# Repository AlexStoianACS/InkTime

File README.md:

## InkTime

Smartwatch ieftin si open source.

### Power Management

Charger LiPo: BQ25180

Regulator 3.3V: RT6160

Fuel gauge: MAX17048

#### Interfata

I2C (SDA/SCL bus comun)

Pini INT pentru evenimente (PMIC_INT, ALERT)

### Display (e-paper)

Conector FPC pentru display e-paper

Circuit de drive + PFET pentru power gating (VEPD)

#### Interfata

SPI:

SCK -> P0.02

MOSI -> P0.03

CS -> P0.05

Control:

DC -> P0.15

RST -> P0.16

BUSY -> P0.17

### Senzori

IMU (accelerometru): BMA421

#### Interfata

I2C:

SDA -> P0.06

SCL -> P0.07

### Haptic Feedback

DRV2605L

#### Interfata

I2C (bus comun)

Enable:

HAPTIC_EN -> P0.12

### Butoane

Up -> P0.13

Down -> P0.14

Enter -> P1.00

### Interfata
D+ -> USB DP (nRF52840)

D- -> USB DM (nRF52840)

VBUS -> detect pin

### Schematic

Schematicul l-am realizat pe o singura pagina.

Toate rezistentele sunt SMD, in capsula 0201. Toate condensatoarele sunt SMD, cele cu valori mai mici sau egale cu 100nF sunt in capsula 0201, cele cu valori mai mari de 100nF sunt 0402.

Am ignorat erorile de ERC de genul "Power pin X connected to Y" sau "Only one pin on net X".

### PCB

PCB-ul este de tip 2-layer si am facut rutarea pe ambele parti, in timp ce componentele sunt doar pe top.

Am plasat butoanele, usb-c connector si e-paper display connector pentru a se alinia cu marginile corespunzator.

Condensatoarele de decuplare (100nF) au fost plasate cat mai aproape de pinii de alimentare. De asemenea, cristalele au fost plasate cat mai aproape de MCU.

Am izolat antena de restul circuitului, nu am trasat rute pe top / bottom unde se afla si nu am facut "polygon pour" in acea zona. Pad-ul "2" a fost plasat in exterior.

Rutele au grosimea 0.3mm pentru semnalele de tip "POWER" si 0.15mm in rest. In anumite cazuri am scazut grosimea pentru a le putea strecura prin anumite locuri.

M-am ajutat de "escape routing" prin plasarea unui via direct pe pin / pad si inceperea rutarii direct pe bottom.

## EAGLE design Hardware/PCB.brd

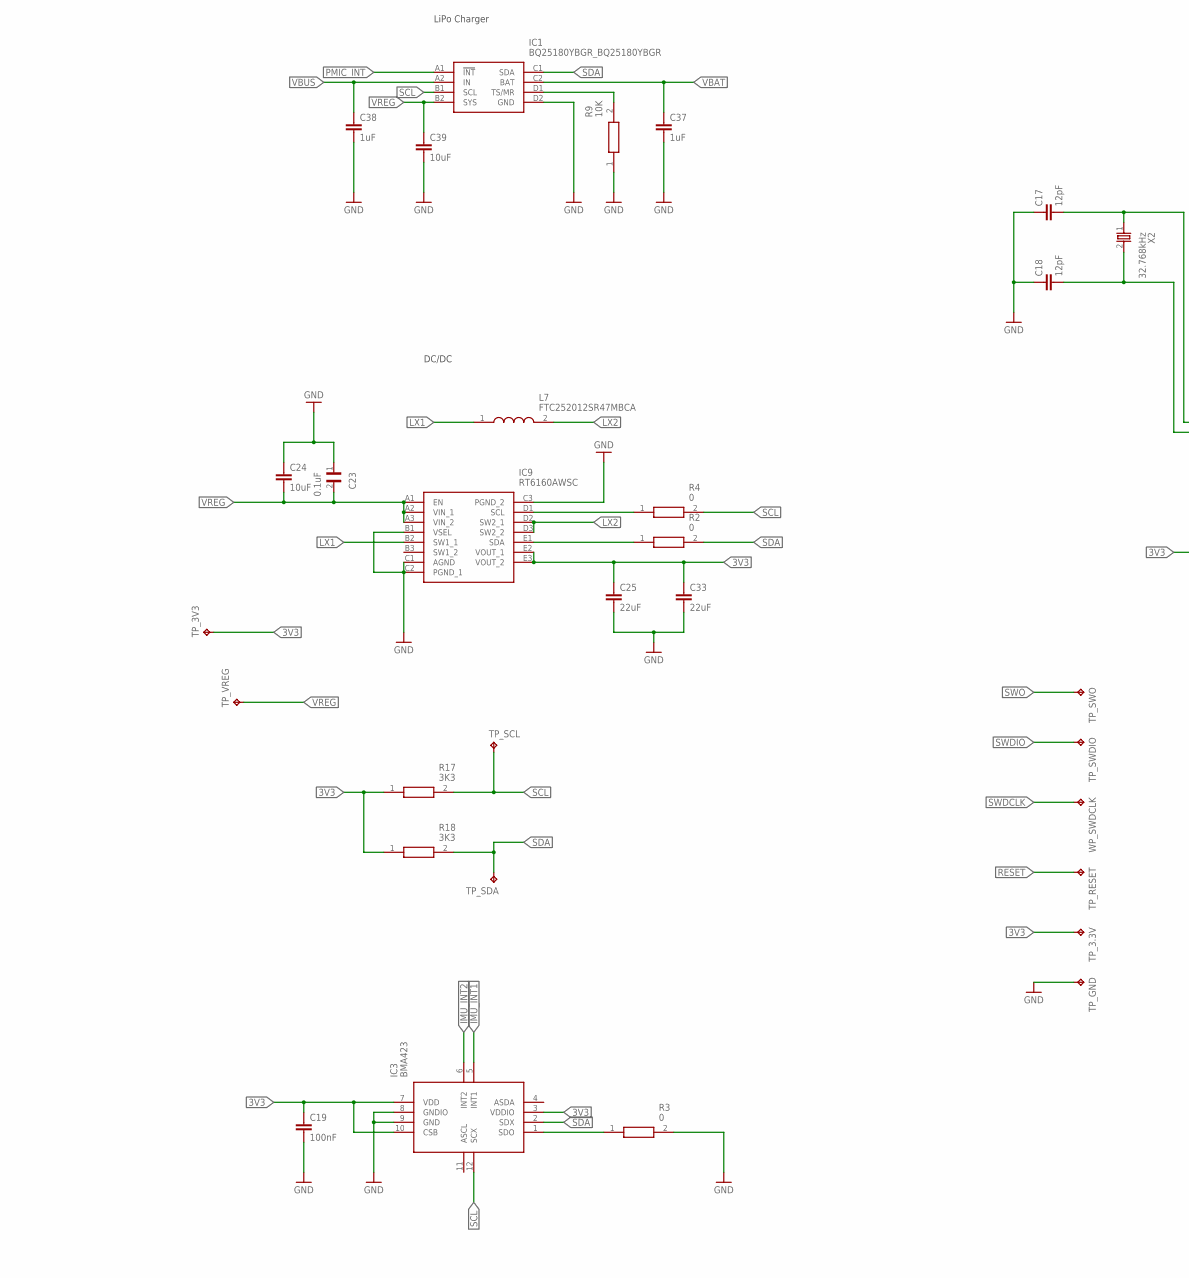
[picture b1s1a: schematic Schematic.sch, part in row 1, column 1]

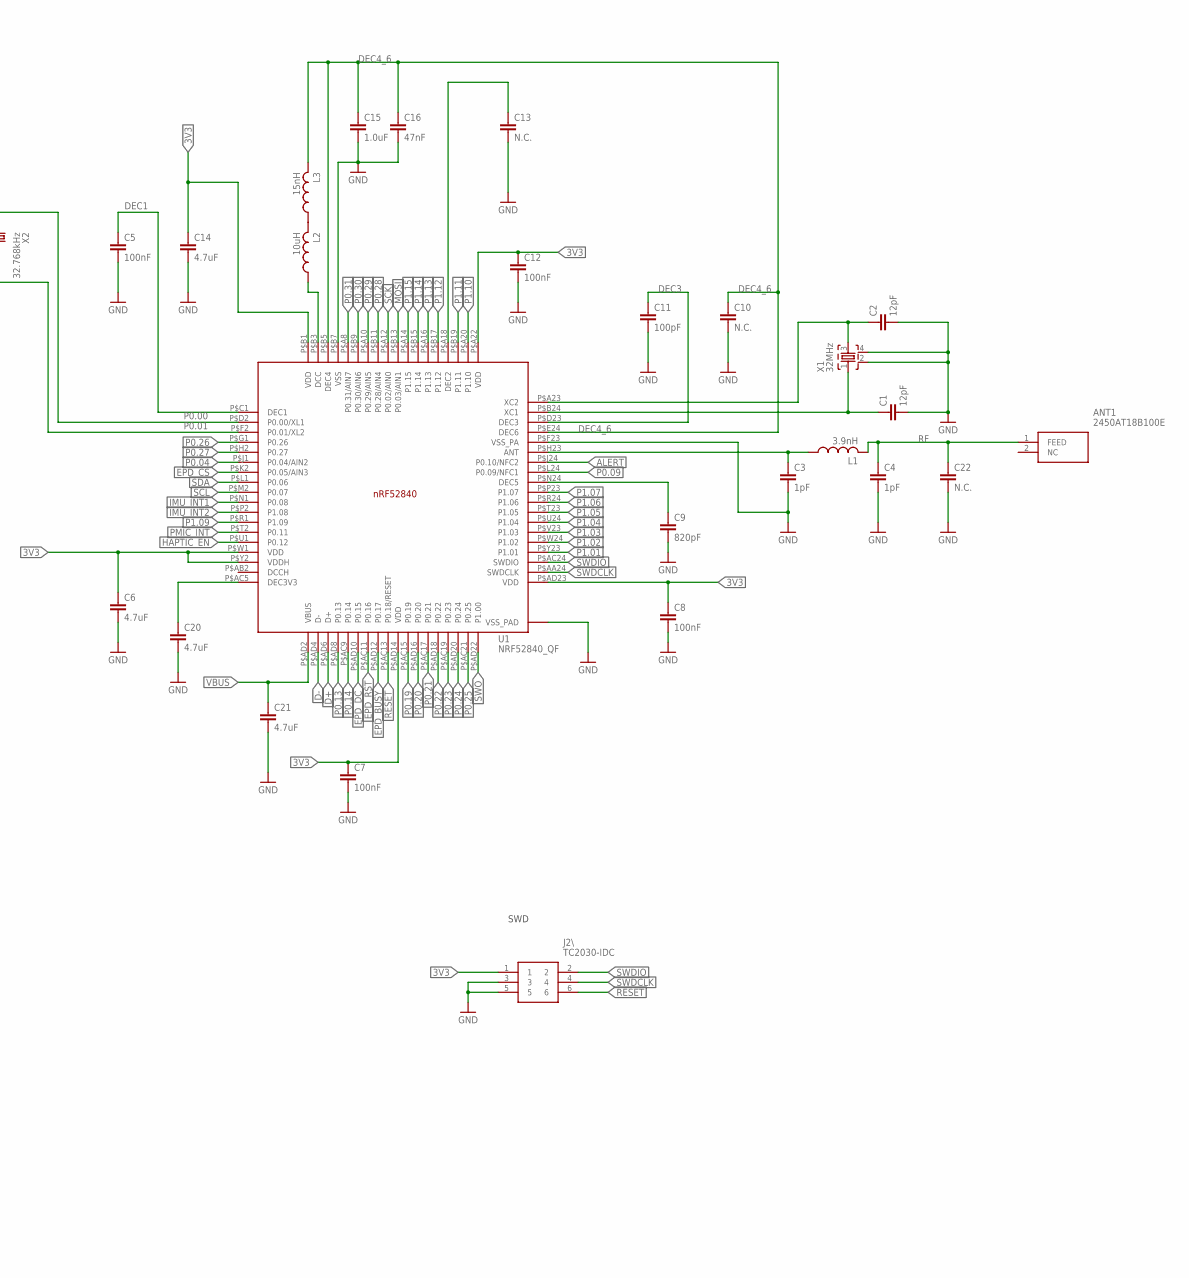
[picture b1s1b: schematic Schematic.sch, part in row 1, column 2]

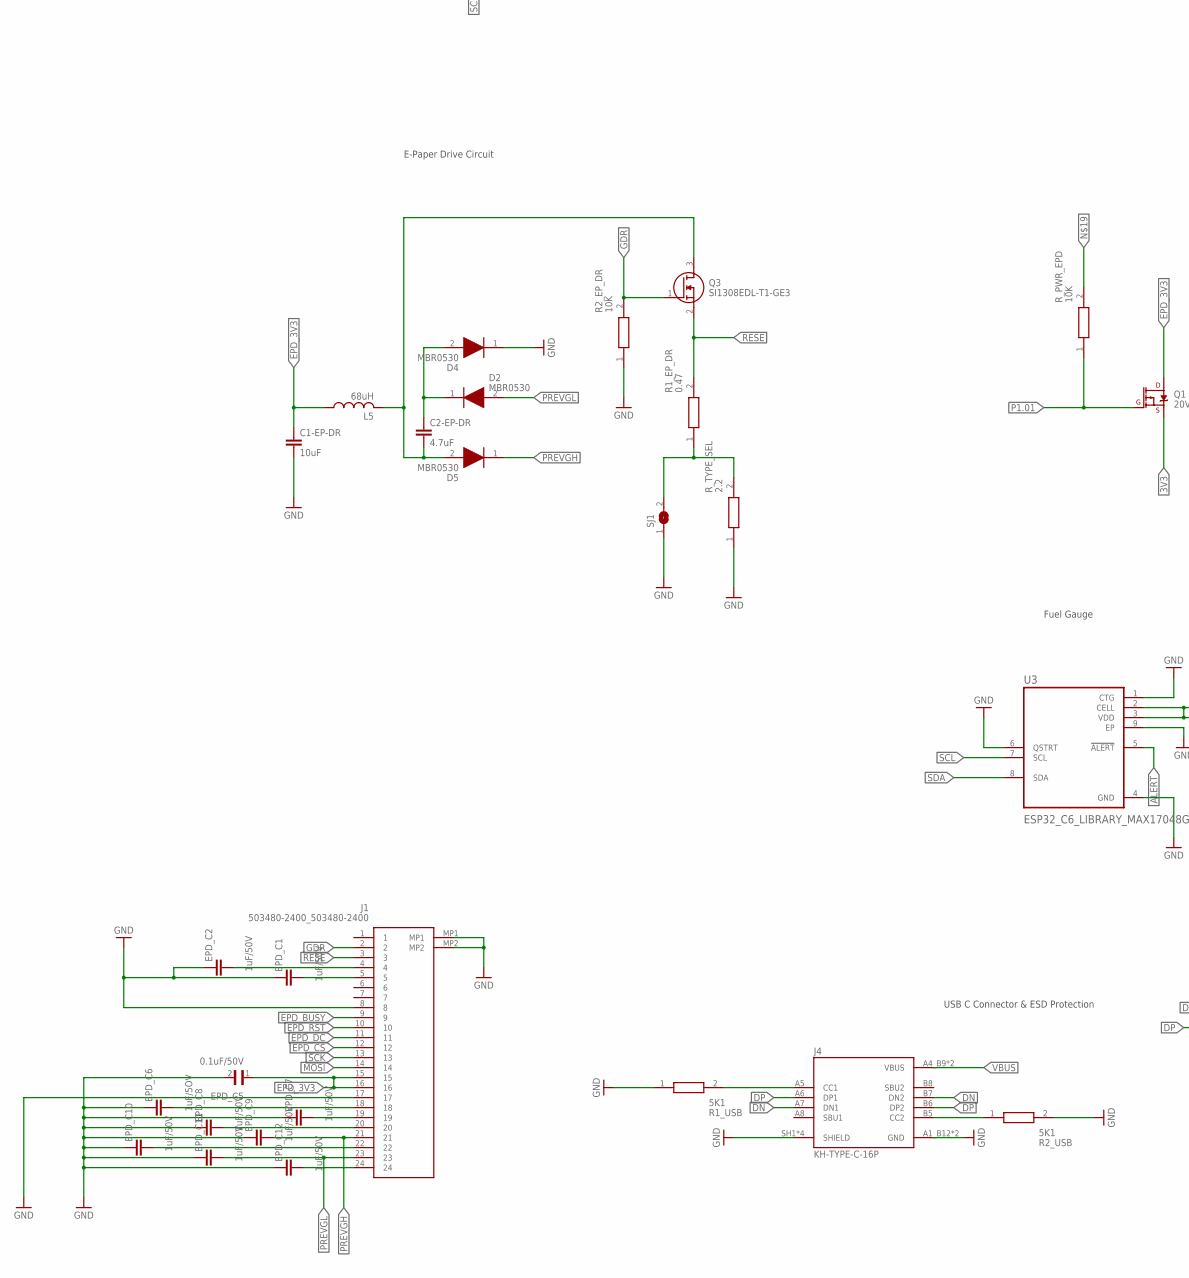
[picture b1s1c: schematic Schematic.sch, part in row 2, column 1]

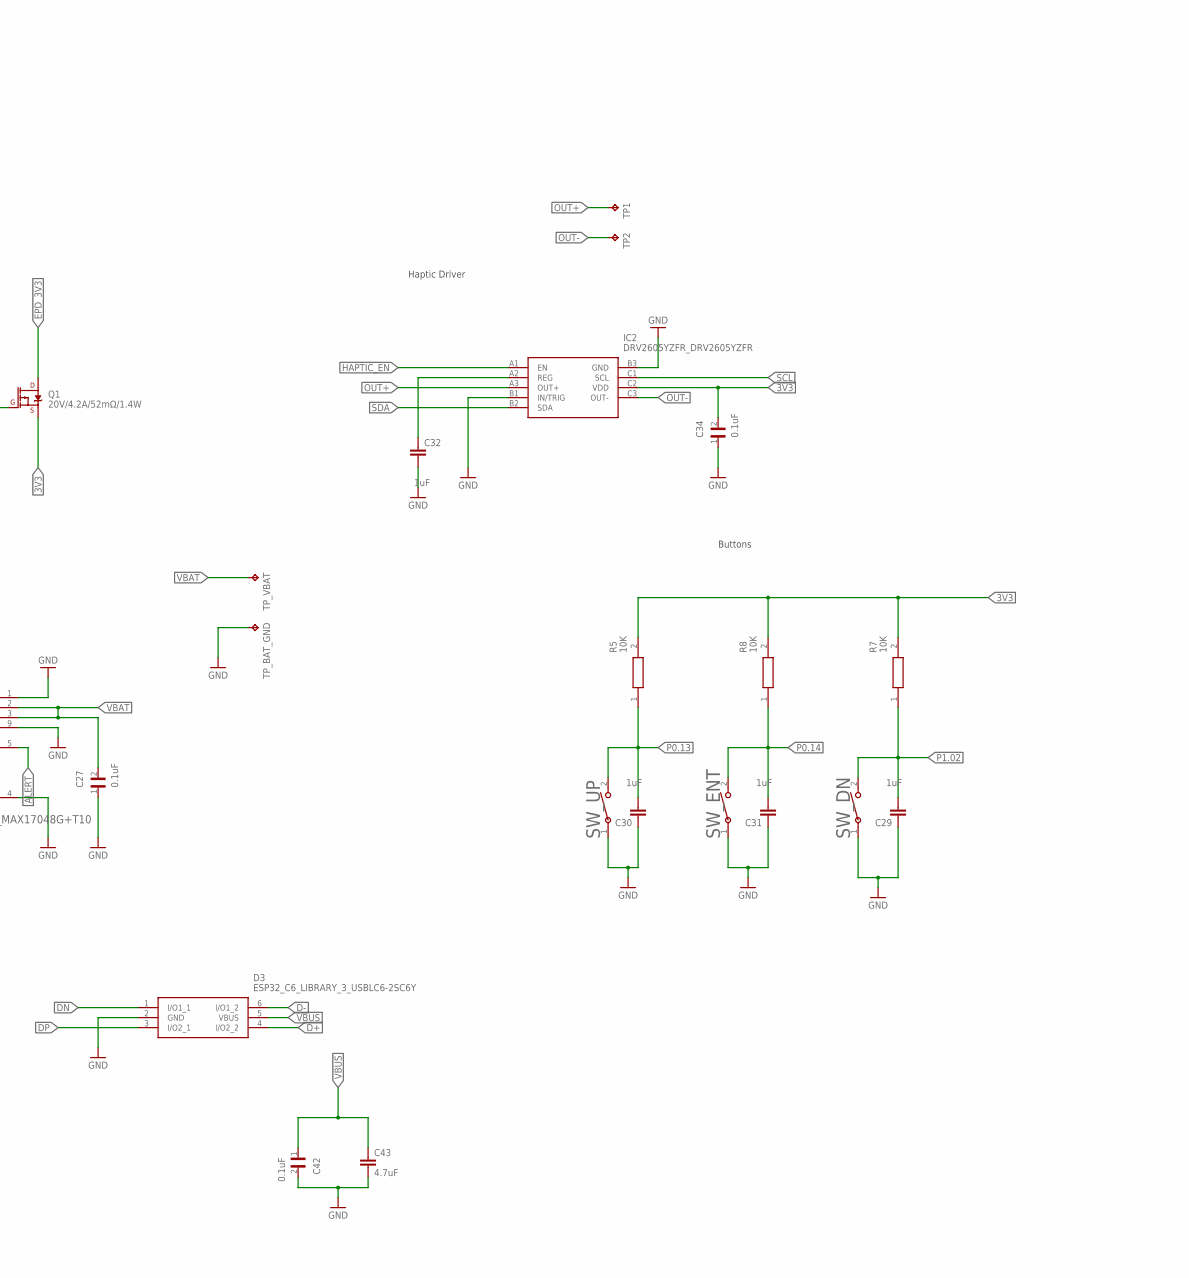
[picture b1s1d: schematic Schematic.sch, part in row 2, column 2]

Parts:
ANT1: 2450AT18B100E; 2450AT18B100E_ANTC3216X140N
C1, C2, C17, C18: 12pF; NORDIC_NRF_3_RESC0201_L
C1-EP-DR, C24, C39: 10uF; ESP32_C6_LIBRARY_1_ESP32_WROVER_EAGLE-LTSPICE_C0402
C2-EP-DR, C6, C14, C20, C21, C43: 4.7uF; ESP32_C6_LIBRARY_1_ESP32_WROVER_EAGLE-LTSPICE_C0402
C3, C4: 1pF; NORDIC_NRF_3_RESC0201_L
C5, C7, C8, C12, C19: 100nF; NORDIC_NRF_3_RESC0201_L
C9: 820pF; NORDIC_NRF_3_RESC0201_L
C10, C13, C22: N.C.; ESP32_C6_LIBRARY_1_ESP32_WROVER_EAGLE-LTSPICE_C0402
C11: 100pF; NORDIC_NRF_3_RESC0201_L
C15: 1.0uF; ESP32_C6_LIBRARY_1_ESP32_WROVER_EAGLE-LTSPICE_C0402
C16: 47nF; NORDIC_NRF_3_RESC0201_L
C23, C27, C34, C42: 0.1uF; GRM011R60J152KE01L_2_CAPC0201X13N
C25, C33: 22uF; ESP32_C6_LIBRARY_1_ESP32_WROVER_EAGLE-LTSPICE_C0402
C29, C30, C31, C32, C37, C38: 1uF; ESP32_C6_LIBRARY_1_ESP32_WROVER_EAGLE-LTSPICE_C0402
D2, D4, D5: MBR0530; ESP32_C6_LIBRARY_5_SOD3716X135N
D3: ESP32_C6_LIBRARY_3_USBLC6-2SC6Y; ESP32_C6_LIBRARY_3_SOT95P280X145-6N
EPD_C1, EPD_C2, EPD_C7, EPD_C8, EPD_C9, EPD_C10, EPD_C11, EPD_C12: 1uF/50V; ESP32_C6_LIBRARY_1_ESP32_WROVER_EAGLE-LTSPICE_C0402
EPD_C5: 0.1uF/50V; GRM011R60J152KE01L_2_CAPC0201X13N
EPD_C6: 1uF/5OV; ESP32_C6_LIBRARY_1_ESP32_WROVER_EAGLE-LTSPICE_C0402
IC1: BQ25180YBGR_BQ25180YBGR; BQ25180YBGR_BGA8C40P2X4_100X155X50
IC2: DRV2605YZFR_DRV2605YZFR; DRV2605YZFR_BGA9C50P3X3_144X144X62
IC3: BMA423; BMA423_BMA423
IC9: RT6160AWSC; RT6160AWSC_BGA15C40P3X5_140X230X60
J1: 503480-2400_503480-2400; 503480-2400_5034802400
J2\: TC2030-IDC; TC2030-IDC_TC2030IDC
J4: KH-TYPE-C-16P; KH-TYPE-C-16P_KINGHELM_KH-TYPE-C-16P
L1: 3.9nH; NORDIC_NRF_2_RESC0402_L
L2: 10uH; NORDIC_NRF_2_RESC0402_L
L3: 15nH; NORDIC_NRF_2_RESC0402_L
L5: 68uH; NORDIC_NRF_2_RESC0402_L
L7: FTC252012SR47MBCA; MLP2016SR47MT0S1_INDC2016X100N
Q1: 20V/4.2A/52mΩ/1.4W; ESP32_C6_LIBRARY_4_ESP32_C6_LIBRARY_4_ESP32_C6_LIBRARY_4_ES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
Q3: SI1308EDL-T1-GE3; ESP32_C6_LIBRARY_6_SOT65P210X110-3N
R1_EP_DR: 0.47; CPF0201D7K68C1_0201
R1_USB, R2_USB: 5K1; CPF0201D7K68C1_0201
R2, R3, R4: 0; CPF0201D7K68C1_0201
R2_EP_DR, R5, R7, R8, R9: 10K; CPF0201D7K68C1_0201
R17, R18: 3K3; CPF0201D7K68C1_0201
R_PWR_EPD: 10K; CPF0201D7K68C1_0201
R_TYPE_SEL: 2.2; CPF0201D7K68C1_0201
SJ1: SJ; ESP32_C6_LIBRARY_7_JUMPER_SJ
SW_DN: 2025-10-22_07-23-44_LIBRARY_EVP-AKE31ASW_EVP-AKE3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; 2025-10-22_07-23-44_LIBRARY_SW_EVP-AKE31A_PAN
SW_ENT: 2025-10-22_07-23-44_LIBRARY_EVP-AKE31ASW_EVP-AKE3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; 2025-10-22_07-23-44_LIBRARY_SW_EVP-AKE31A_PAN
SW_UP: 2025-10-22_07-23-44_LIBRARY_EVP-AKE31ASW_EVP-AKE3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; 2025-10-22_07-23-44_LIBRARY_SW_EVP-AKE31A_PAN
TP1, TP2: HECTOR_WATCH_1_TPTP20R; HECTOR_WATCH_1_TP20R
TP_3.3V, TP_3V3: HECTOR_WATCH_1_TPTP20R; HECTOR_WATCH_1_TP20R
TP_BAT_GND: HECTOR_WATCH_1_TPTP20R; HECTOR_WATCH_1_TP20R
TP_GND: HECTOR_WATCH_1_TPTP20R; HECTOR_WATCH_1_TP20R
TP_RESET: HECTOR_WATCH_1_TPTP20R; HECTOR_WATCH_1_TP20R
TP_SCL: HECTOR_WATCH_1_TPTP20R; HECTOR_WATCH_1_TP20R
TP_SDA: HECTOR_WATCH_1_TPTP20R; HECTOR_WATCH_1_TP20R
TP_SWDIO: HECTOR_WATCH_1_TPTP20R; HECTOR_WATCH_1_TP20R
TP_SWO: HECTOR_WATCH_1_TPTP20R; HECTOR_WATCH_1_TP20R
TP_VBAT: HECTOR_WATCH_1_TPTP20R; HECTOR_WATCH_1_TP20R
TP_VREG: HECTOR_WATCH_1_TPTP20R; HECTOR_WATCH_1_TP20R
U1: NRF52840_QF; NORDIC_NRF_4_AQFN50P700X700X85_HS-74N
U3: ESP32_C6_LIBRARY_MAX17048G+T10; ESP32_C6_LIBRARY_SON50P200X200X80-9N
WP_SWDCLK: HECTOR_WATCH_1_TPTP20R; HECTOR_WATCH_1_TP20R
X1: 32MHz; NORDIC_NRF_BT-XTAL_2016_N
X2: 32.768kHz; NORDIC_NRF_1_XTAL_3215_N

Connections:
3V3: C6.1, C7.1, C8.1, C12.1, C14.1, C19.1, C25.1, C33.1, C34.2, IC2.C2 (VDD), IC3.3 (VDDIO), IC3.7 (VDD), IC3.10 (CSB), IC9.E2 (VOUT_1), IC9.E3 (VOUT_2), J2\.1, Q1.2 (S), R5.2, R7.2, R8.2, R17.1, R18.1, TP_3.3V.TP, TP_3V3.TP, U1.P$A22 (VDD), U1.P$AD14 (VDD), U1.P$AD23 (VDD), U1.P$B1 (VDD), U1.P$W1 (VDD), U1.P$Y2 (VDDH)
ALERT: U1.P$J24 (P0.10/NFC2), U3.5 (!ALERT)
D+: D3.4 (I/O2_2), U1.P$AD6 (D+)
D-: D3.6 (I/O1_2), U1.P$AD4 (D-)
DEC1: C5.1, U1.P$C1 (DEC1)
DEC3: C11.1, U1.P$D23 (DEC3)
DEC4_6: C10.1, C15.1, C16.1, L3.2, U1.P$B5 (DEC4), U1.P$E24 (DEC6)
DN: D3.1 (I/O1_1), J4.A7 (DN1), J4.B7 (DN2)
DP: D3.3 (I/O2_1), J4.A6 (DP1), J4.B6 (DP2)
EPD_3V3: C1-EP-DR.1, EPD_C5.1, J1.15, J1.16, L5.1, Q1.3 (D)
EPD_BUSY: J1.9, U1.P$AD12 (P0.17)
EPD_CS: J1.12, U1.P$K2 (P0.05/AIN3)
EPD_DC: J1.11, U1.P$AD10 (P0.15)
EPD_RST: J1.10, U1.P$AC11 (P0.16)
GDR: J1.2, Q3.1 (G), R2_EP_DR.2
GND: C1.2, C1-EP-DR.2, C2.2, C3.2, C4.2, C5.2, C6.2, C7.2, C8.2, C9.2, C10.2, C11.2, C12.2, C13.2, C14.2, C15.2, C16.2, C17.1, C18.1, C19.2, C20.2, C21.2, C22.2, C23.1, C24.1, C25.2, C27.1, C29.1, C30.1, C31.1, C32.2, C33.2, C34.1, C37.2, C38.2, C39.2, C42.2, C43.2, D3.2 (GND), D4.1 (K), EPD_C1.1, EPD_C2.1, EPD_C5.2, EPD_C6.1, EPD_C7.1, EPD_C8.1, EPD_C9.1, EPD_C10.1, EPD_C11.1, EPD_C12.1, IC1.D2 (GND), IC2.B1 (IN/TRIG), IC2.B3 (GND), IC3.8 (GNDIO), IC3.9 (GND), IC9.B1 (VSEL), IC9.C1 (AGND), IC9.C2 (PGND_1), IC9.C3 (PGND_2), J1.8, J1.17, J1.MP1, J1.MP2, J2\.3, J2\.5, J4.A1_B12 (GND), J4.A12_B1 (GND), J4.SH1 (SHIELD), J4.SH2 (SHIELD), J4.SH3 (SHIELD), J4.SH4 (SHIELD), R1_USB.1, R2_EP_DR.1, R2_USB.2, R3.2, R9.1, R_TYPE_SEL.1, SJ1.1, SW_DN.1, SW_ENT.1, SW_UP.1, TP_BAT_GND.TP, TP_GND.TP, U1.P$74 (VSS_PAD), U1.P$75 (VSS_PAD), U1.P$76 (VSS_PAD), U1.P$77 (VSS_PAD), U1.P$78 (VSS_PAD), U1.P$79 (VSS_PAD), U1.P$80 (VSS_PAD), U1.P$81 (VSS_PAD), U1.P$82 (VSS_PAD), U1.P$83 (VSS_PAD), U1.P$84 (VSS_PAD), U1.P$85 (VSS_PAD), U1.P$86 (VSS_PAD), U1.P$87 (VSS_PAD), U1.P$88 (VSS_PAD), U1.P$89 (VSS_PAD), U1.P$90 (VSS_PAD), U1.P$B7 (VSS), U1.P$F23 (VSS_PA), U3.1 (CTG), U3.4 (GND), U3.6 (QSTRT), U3.9 (EP), X1.2, X1.4
HAPTIC_EN: IC2.A1 (EN), U1.P$U1 (P0.12)
IMU_INT1: IC3.5 (INT1), U1.P$N1 (P0.08)
IMU_INT2: IC3.6 (INT2), U1.P$P2 (P1.08)
LX1: IC9.B2 (SW1_1), L7.1
LX2: IC9.D2 (SW2_1), IC9.D3 (SW2_2), L7.2
MOSI: J1.14, U1.P$B13 (P0.03/AIN1)
unnamed: J4.A5 (CC1), R1_USB.2
unnamed: C2-EP-DR.2, D5.2 (A), L5.2, Q3.3 (D)
unnamed: L2.2, L3.1
unnamed: IC3.1 (SDO), R3.1
unnamed: C2.1, U1.P$A23 (XC2), X1.3
unnamed: IC1.D1 (TS/MR), R9.2
unnamed: L2.1, U1.P$B3 (DCC)
unnamed: IC9.E1 (SDA), R2.1
unnamed: C1.1, U1.P$B24 (XC1), X1.1
unnamed: IC9.D1 (SCL), R4.1
unnamed: C13.1, U1.P$A18 (DEC2)
unnamed: C3.1, L1.1, U1.P$H23 (ANT)
unnamed: C20.1, U1.P$AC5 (DEC3V3)
unnamed: C2-EP-DR.1, D2.1 (K), D4.2 (A)
unnamed: C32.1, IC2.A2 (REG)
unnamed: C9.1, U1.P$N24 (DEC5)
unnamed: R1_EP_DR.1, R_TYPE_SEL.2, SJ1.2
unnamed: EPD_C2.2, J1.4
unnamed: EPD_C1.2, J1.5
unnamed: J4.B5 (CC2), R2_USB.1
unnamed: EPD_C12.2, J1.24
unnamed: EPD_C10.2, J1.22
unnamed: EPD_C8.2, J1.20
unnamed: EPD_C7.2, J1.19
unnamed: EPD_C6.2, J1.18
OUT+: IC2.A3 (OUT+), TP1.TP
OUT-: IC2.C3 (OUT-), TP2.TP
P0.00: C17.2, U1.P$D2 (P0.00/XL1), X2.1
P0.01: C18.2, U1.P$F2 (P0.01/XL2), X2.2
P0.04: U1.P$J1 (P0.04/AIN2)
P0.09: U1.P$L24 (P0.09/NFC1)
P0.13: C30.2, R5.1, SW_UP.2, U1.P$AD8 (P0.13)
P0.14: C31.2, R8.1, SW_ENT.2, U1.P$AC9 (P0.14)
P0.19: U1.P$AC15 (P0.19)
P0.20: U1.P$AD16 (P0.20)
P0.21: U1.P$AC17 (P0.21)
P0.22: U1.P$AD18 (P0.22)
P0.23: U1.P$AC19 (P0.23)
P0.24: U1.P$AD20 (P0.24)
P0.25: U1.P$AC21 (P0.25)
P0.26: U1.P$G1 (P0.26)
P0.27: U1.P$H2 (P0.27)
P0.28: U1.P$B11 (P0.28/AIN4)
P0.29: U1.P$A10 (P0.29/AIN5)
P0.30: U1.P$B9 (P0.30/AIN6)
P0.31: U1.P$A8 (P0.31/AIN7)
P1.01: Q1.1 (G), R_PWR_EPD.1, U1.P$Y23 (P1.01)
P1.02: C29.2, R7.1, SW_DN.2, U1.P$W24 (P1.02)
P1.03: U1.P$V23 (P1.03)
P1.04: U1.P$U24 (P1.04)
P1.05: U1.P$T23 (P1.05)
P1.06: U1.P$R24 (P1.06)
P1.07: U1.P$P23 (P1.07)
P1.09: U1.P$R1 (P1.09)
P1.10: U1.P$A20 (P1.10)
P1.11: U1.P$B19 (P1.11)
P1.12: U1.P$B17 (P1.12)
P1.13: U1.P$A16 (P1.13)
P1.14: U1.P$B15 (P1.14)
P1.15: U1.P$A14 (P1.15)
PMIC_INT: IC1.A1 (!INT), U1.P$T2 (P0.11)
PREVGH: D5.1 (K), EPD_C9.2, J1.21
PREVGL: D2.2 (A), EPD_C11.2, J1.23
RESE: J1.3, Q3.2 (S), R1_EP_DR.2
RESET: J2\.6, TP_RESET.TP, U1.P$AC13 (P0.18/RESET)
RF: ANT1.1 (FEED), C4.1, C22.1, L1.2
SCK: J1.13, U1.P$A12 (P0.02/AIN0)
SCL: IC1.B1 (SCL), IC2.C1 (SCL), IC3.12 (SCX), R4.2, R17.2, TP_SCL.TP, U1.P$M2 (P0.07), U3.7 (SCL)
SDA: IC1.C1 (SDA), IC2.B2 (SDA), IC3.2 (SDX), R2.2, R18.2, TP_SDA.TP, U1.P$L1 (P0.06), U3.8 (SDA)
SWDCLK: J2\.4, U1.P$AA24 (SWDCLK), WP_SWDCLK.TP
SWDIO: J2\.2, TP_SWDIO.TP, U1.P$AC24 (SWDIO)
SWO: TP_SWO.TP, U1.P$AD22 (P1.00)
VBAT: C27.2, C37.1, IC1.C2 (BAT), TP_VBAT.TP, U3.2 (CELL), U3.3 (VDD)
VBUS: C21.1, C38.1, C42.1, C43.1, D3.5 (VBUS), IC1.A2 (IN), J4.A4_B9 (VBUS), J4.A9_B4 (VBUS), U1.P$AD2 (VBUS)
VREG: C23.2, C24.2, C39.1, IC1.B2 (SYS), IC9.A1 (EN), IC9.A2 (VIN_1), IC9.A3 (VIN_2), TP_VREG.TP

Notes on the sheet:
LiPo Charger
DC/DC
SWD
E-Paper Drive Circuit
Haptic Driver
Fuel Gauge
Buttons
USB C Connector & ESD Protection

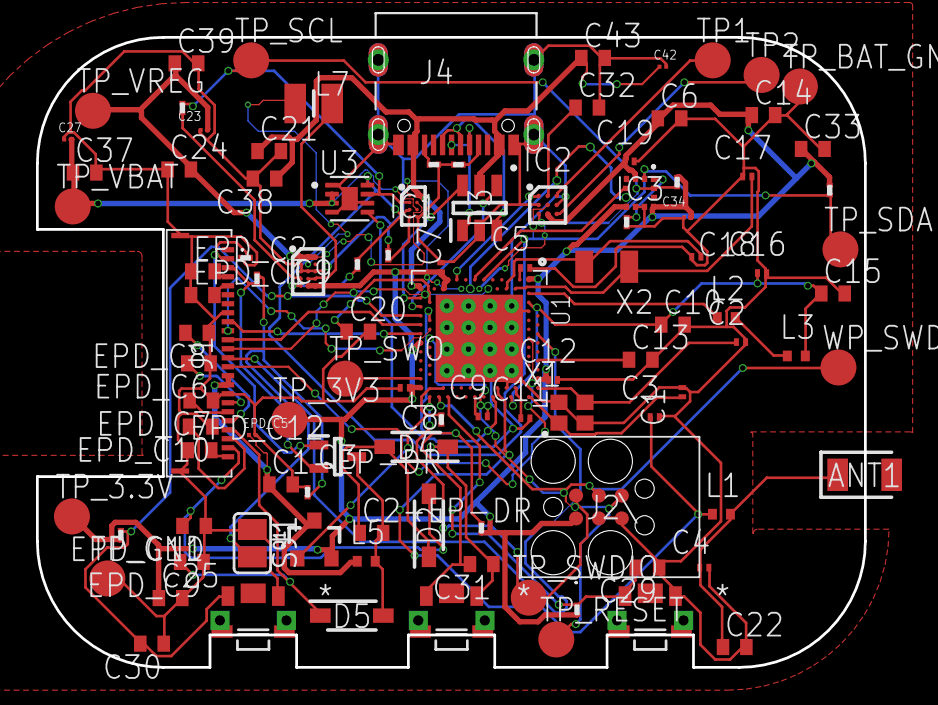
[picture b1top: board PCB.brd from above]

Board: 2 copper layers, 46.0 x 35.0 mm, 105 parts (0 on the bottom side), 70 nets.

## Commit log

2026-04-10 Engineering Validation (EVT)
2026-04-21 Design Validation (DVT)

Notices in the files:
parts and their libraries:
COPYRIGHT: Copyright (C) 2025 Ultra Librarian. All rights reserved.
